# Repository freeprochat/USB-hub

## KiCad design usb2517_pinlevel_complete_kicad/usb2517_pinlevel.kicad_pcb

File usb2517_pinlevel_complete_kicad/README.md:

# USB2517 pin-level KiCad project

This package contains a normal legacy KiCad schematic with a custom cache library, a 64-pin USB2517 symbol, explicit pin-to-net connectivity matrix, a four-layer PCB with pads, named nets, differential routes, high-current power routes and GND/5V zones. KiCad 6-9 can open and convert the legacy `.sch` to modern `.kicad_sch`.

Important: The PCB is a complete connected engineering draft, not a production release. The Molex and TI footprints are dimensionally tagged but are not authenticated manufacturer ECAD downloads. Run ERC/DRC after conversion on a workstation with KiCad installed, confirm all footprint land patterns from the current drawings, tune USB impedance to the fab stackup, and perform power/thermal/USB compliance testing.

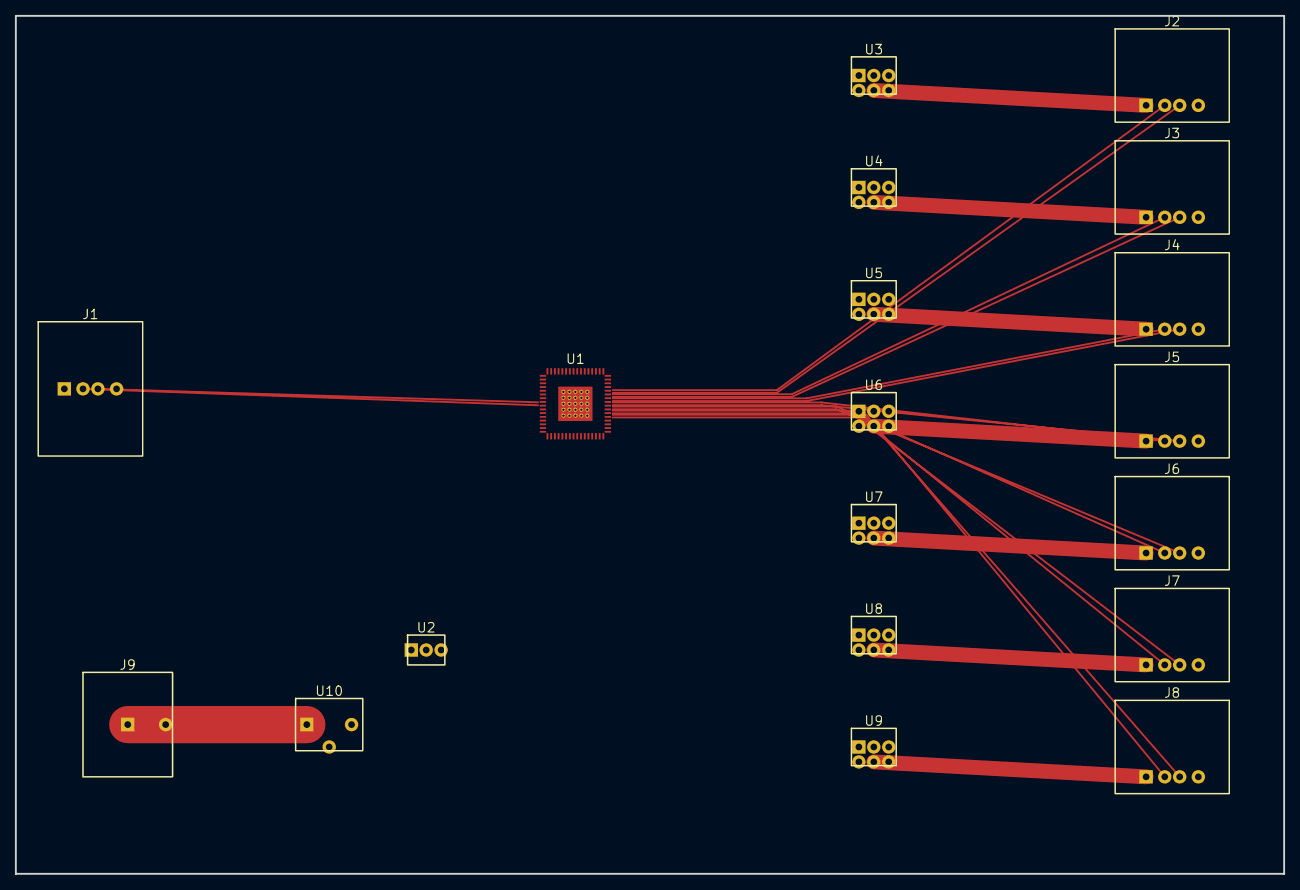
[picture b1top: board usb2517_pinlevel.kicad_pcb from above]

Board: 4 copper layers, 170.0 x 115.0 mm, 19 parts (0 on the bottom side), 42 nets.

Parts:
J1: MOLEX_480370001
J2, J3, J4, J5, J6, J7, J8: GCT_USB1086
J9: PHOENIX_1715721
U1: USB2517_JZX_QFN64_EP
U2: AP2112K
U3, U4, U5, U6, U7, U8, U9: AP22653
U10: TPS548B22_RVF40

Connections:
3V3: U1.5, U1.10, U1.24, U1.46, U1.52, U1.57, U1.64, U2.3
5V_LOCAL: U2.1, U3.1, U4.1, U5.1, U6.1, U7.1, U8.1, U9.1, U10.2
12V_IN: J9.1, U10.1
GND: J1.4, J2.4, J3.4, J4.4, J5.4, J6.4, J7.4, J8.4, J9.2, U1.13, U1.14, U1.15, U1.16, U1.17, U1.18, U1.19, U1.25, U1.31, U1.32, U1.33, U1.34, U1.40, U1.41, U1.42, U1.43, U1.45, U1.47, U1.48, U1.49, U1.50, U1.51, U1.60, U1.61, U1.62, U1.63, U1.65, U2.2, U3.3, U3.6, U4.3, U4.6, U5.3, U5.6, U6.3, U6.6, U7.3, U7.6, U8.3, U8.6, U9.3, U9.6, U10.3
OCS1_N: U1.28, U3.4
OCS2_N: U1.27, U4.4
OCS3_N: U1.22, U5.4
OCS4_N: U1.21, U6.4
OCS5_N: U1.35, U7.4
OCS6_N: U1.38, U8.4
OCS7_N: U1.37, U9.4
PRTPWR1: U1.29, U3.2
PRTPWR2: U1.26, U4.2
PRTPWR3: U1.23, U5.2
PRTPWR4: U1.20, U6.2
PRTPWR5: U1.30, U7.2
PRTPWR6: U1.39, U8.2
PRTPWR7: U1.36, U9.2
USB0_D+: J1.3, U1.59
USB0_D-: J1.2, U1.58
USB1_D+: J2.3, U1.2
USB1_D-: J2.2, U1.1
USB2_D+: J3.3, U1.4
USB2_D-: J3.2, U1.3
USB3_D+: J4.3, U1.7
USB3_D-: J4.2, U1.6
USB4_D+: J5.3, U1.9
USB4_D-: J5.2, U1.8
USB5_D+: J6.3, U1.12
USB5_D-: J6.2, U1.11
USB6_D+: J7.3, U1.54
USB6_D-: J7.2, U1.53
USB7_D+: J8.3, U1.56
USB7_D-: J8.2, U1.55
VBUS_P1: J2.1, U3.5
VBUS_P2: J3.1, U4.5
VBUS_P3: J4.1, U5.5
VBUS_P4: J5.1, U6.5
VBUS_P5: J6.1, U7.5
VBUS_P6: J7.1, U8.5
VBUS_P7: J8.1, U9.5
VBUS_UP: J1.1, U1.44

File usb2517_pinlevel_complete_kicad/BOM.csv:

Reference,Part,Footprint
U1,USB2517-JZX,usb_hub:USB2517_JZX_QFN64_EP
J1,Molex 480370001,usb_hub:MOLEX_480370001
J2-J8,GCT USB1086-GF-B,usb_hub:GCT_USB1086
J9,Phoenix 1715721,usb_hub:PHOENIX_1715721
U3-U9,AP22653W6-7,usb_hub:AP22653
U10,TPS548B22RVFR,usb_hub:TPS548B22_RVF40
